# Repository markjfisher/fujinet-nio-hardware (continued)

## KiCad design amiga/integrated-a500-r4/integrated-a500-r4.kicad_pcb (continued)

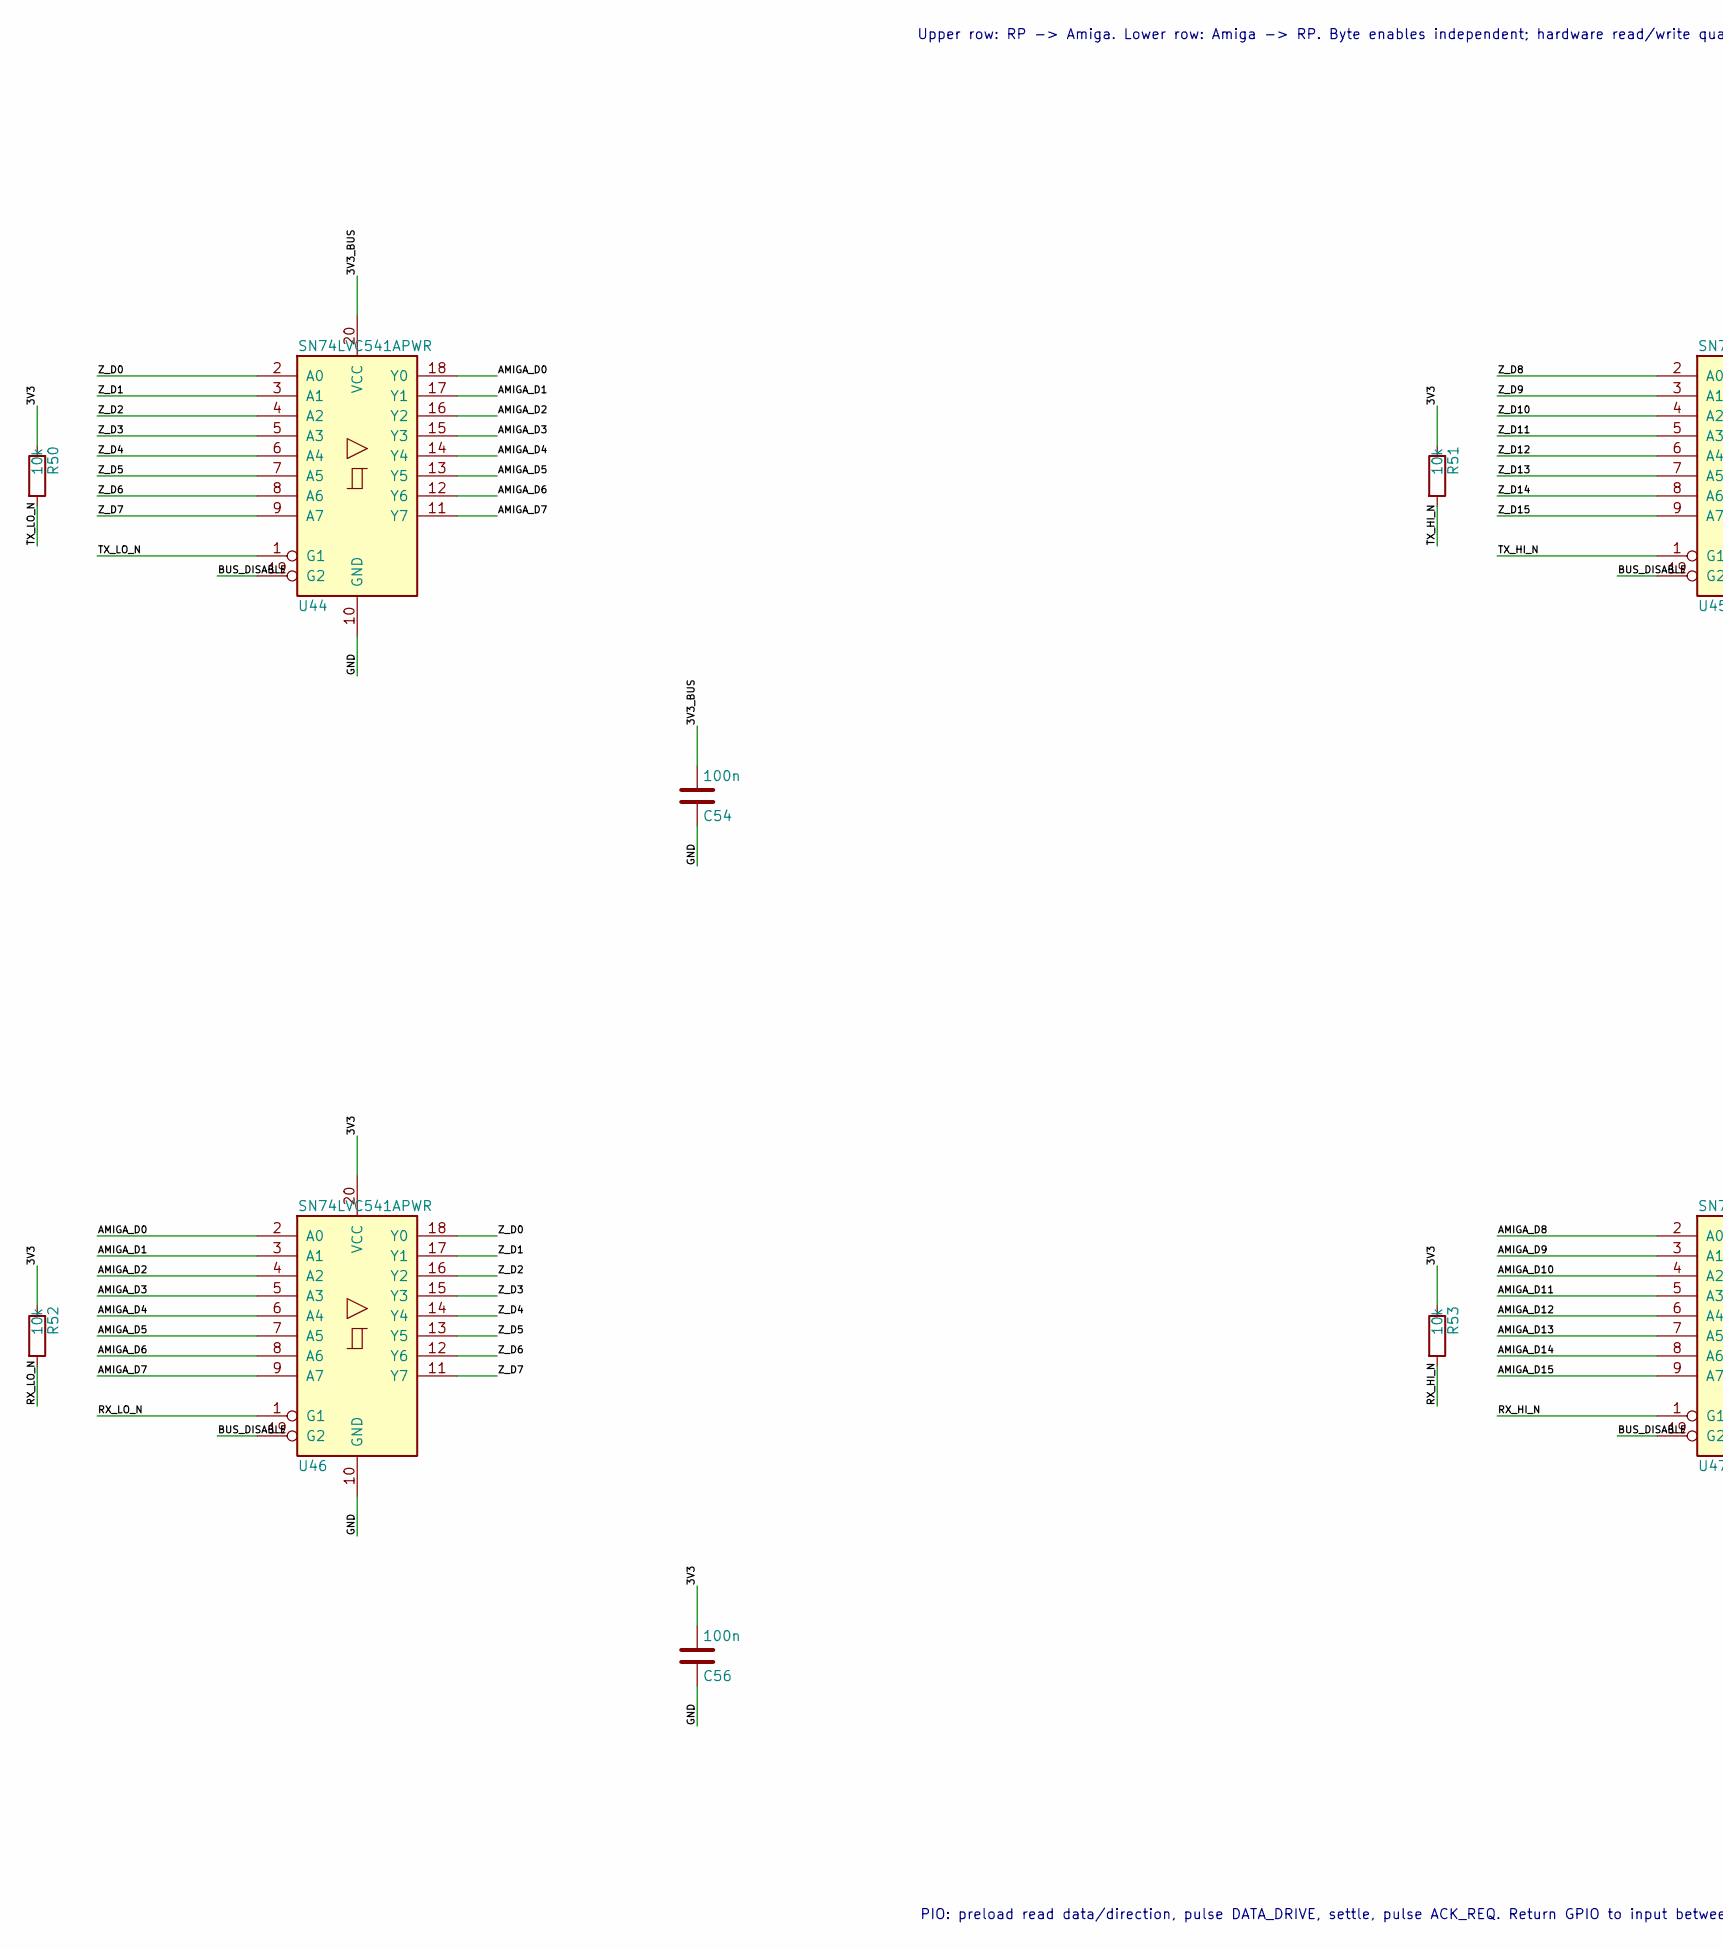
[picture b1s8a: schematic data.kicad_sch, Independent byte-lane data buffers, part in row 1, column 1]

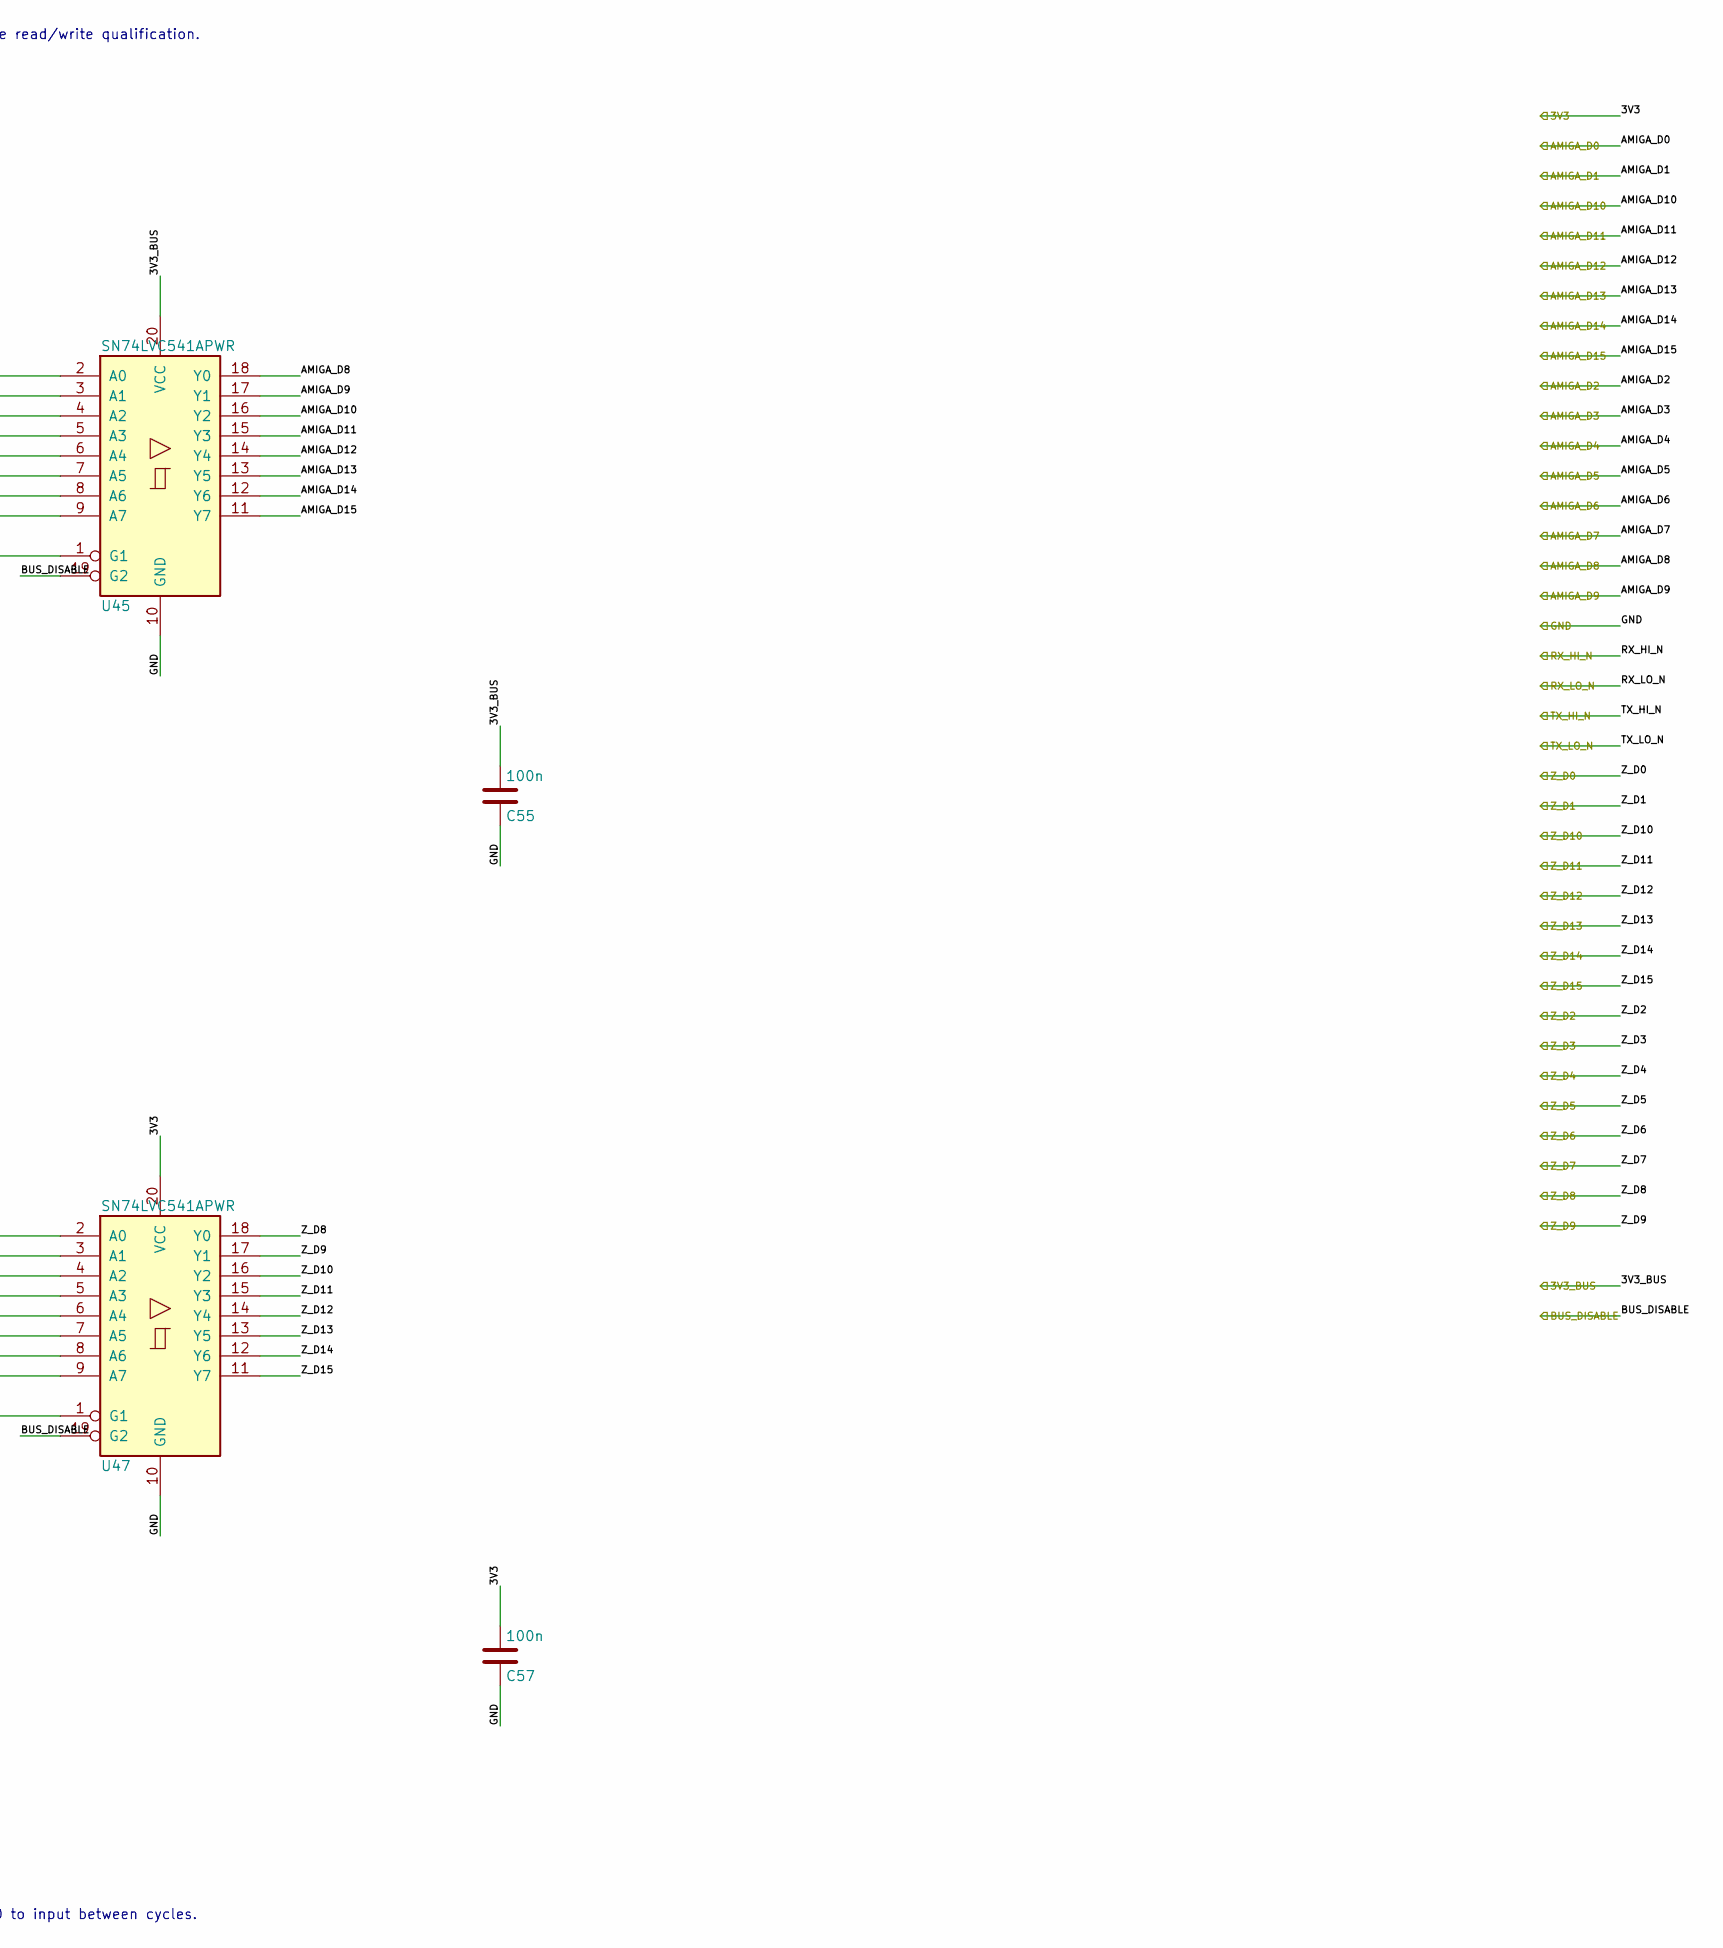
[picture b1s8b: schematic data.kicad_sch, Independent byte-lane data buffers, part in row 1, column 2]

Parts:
C54, C55, C56, C57: 100n; C_0603_1608Metric
R50, R51, R52, R53: 10k; R_0603_1608Metric
U44, U45, U46, U47: SN74LVC541APWR; TSSOP-20_4.4x6.5mm_P0.65mm

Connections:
/3V3: C56.1, C57.1, R50.1, R51.1, R52.1, R53.1, U46.20 (VCC), U47.20 (VCC); also elsewhere on the board
/3V3_BUS: C54.1, C55.1, U44.20 (VCC), U45.20 (VCC); also elsewhere on the board
/AMIGA_D0: U44.18 (Y0), U46.2 (A0); also elsewhere on the board
/AMIGA_D1: U44.17 (Y1), U46.3 (A1); also elsewhere on the board
/AMIGA_D2: U44.16 (Y2), U46.4 (A2); also elsewhere on the board
/AMIGA_D3: U44.15 (Y3), U46.5 (A3); also elsewhere on the board
/AMIGA_D4: U44.14 (Y4), U46.6 (A4); also elsewhere on the board
/AMIGA_D5: U44.13 (Y5), U46.7 (A5); also elsewhere on the board
/AMIGA_D6: U44.12 (Y6), U46.8 (A6); also elsewhere on the board
/AMIGA_D7: U44.11 (Y7), U46.9 (A7); also elsewhere on the board
/AMIGA_D8: U45.18 (Y0), U47.2 (A0); also elsewhere on the board
/AMIGA_D9: U45.17 (Y1), U47.3 (A1); also elsewhere on the board
/AMIGA_D10: U45.16 (Y2), U47.4 (A2); also elsewhere on the board
/AMIGA_D11: U45.15 (Y3), U47.5 (A3); also elsewhere on the board
/AMIGA_D12: U45.14 (Y4), U47.6 (A4); also elsewhere on the board
/AMIGA_D13: U45.13 (Y5), U47.7 (A5); also elsewhere on the board
/AMIGA_D14: U45.12 (Y6), U47.8 (A6); also elsewhere on the board
/AMIGA_D15: U45.11 (Y7), U47.9 (A7); also elsewhere on the board
/BUS_DISABLE: U44.19 (G2), U45.19 (G2), U46.19 (G2), U47.19 (G2); also elsewhere on the board
/RX_HI_N: R53.2, U47.1 (G1); also elsewhere on the board
/RX_LO_N: R52.2, U46.1 (G1); also elsewhere on the board
/TX_HI_N: R51.2, U45.1 (G1); also elsewhere on the board
/TX_LO_N: R50.2, U44.1 (G1); also elsewhere on the board
/Z_D0: U44.2 (A0), U46.18 (Y0); also elsewhere on the board
/Z_D1: U44.3 (A1), U46.17 (Y1); also elsewhere on the board
/Z_D2: U44.4 (A2), U46.16 (Y2); also elsewhere on the board
/Z_D3: U44.5 (A3), U46.15 (Y3); also elsewhere on the board
/Z_D4: U44.6 (A4), U46.14 (Y4); also elsewhere on the board
/Z_D5: U44.7 (A5), U46.13 (Y5); also elsewhere on the board
/Z_D6: U44.8 (A6), U46.12 (Y6); also elsewhere on the board
/Z_D7: U44.9 (A7), U46.11 (Y7); also elsewhere on the board
/Z_D8: U45.2 (A0), U47.18 (Y0); also elsewhere on the board
/Z_D9: U45.3 (A1), U47.17 (Y1); also elsewhere on the board
/Z_D10: U45.4 (A2), U47.16 (Y2); also elsewhere on the board
/Z_D11: U45.5 (A3), U47.15 (Y3); also elsewhere on the board
/Z_D12: U45.6 (A4), U47.14 (Y4); also elsewhere on the board
/Z_D13: U45.7 (A5), U47.13 (Y5); also elsewhere on the board
/Z_D14: U45.8 (A6), U47.12 (Y6); also elsewhere on the board
/Z_D15: U45.9 (A7), U47.11 (Y7); also elsewhere on the board

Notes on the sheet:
Upper row: RP -> Amiga. Lower row: Amiga -> RP. Byte enables independent; hardware read/write qualification.
PIO: preload read data/direction, pulse DATA_DRIVE, settle, pulse ACK_REQ. Return GPIO to input between cycles.

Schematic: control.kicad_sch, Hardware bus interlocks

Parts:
C70, C73, C75, C80, C81, C82, C86, C87, C88, C91, C93, C94, C95: 100n; C_0603_1608Metric
J60: BUS ARM (normally OPEN); PinHeader_1x02_P2.54mm_Vertical
R63, R64, R65, R66, R67: 10k; R_0603_1608Metric
U61, U66, U71: SN74LVC11APWR; TSSOP-14_4.4x5mm_P0.65mm
U64: SN74LVC04APWR; TSSOP-14_4.4x5mm_P0.65mm
U72, U73, U77, U78: SN74LVC1G10DBVR; SOT-23-6
U79: SN74LVC1G32DBVR; SOT-23-5
U82, U85: SN74LVC1G08DBVR; SOT-23-5
U84, U86: SN74LVC1G74DCUR; VSSOP-8_2.3x2mm_P0.5mm

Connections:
/3V3: C70.1, C73.1, C75.1, C80.1, C81.1, C82.1, C86.1, C87.1, C88.1, C91.1, C93.1, C94.1, C95.1, J60.1, U61.14 (VCC), U64.14 (VCC), U66.14 (VCC), U71.11 (3C), U71.14 (VCC), U72.5 (VCC), U72.6, U73.5 (VCC), U73.6, U77.5 (VCC), U77.6, U78.5 (VCC), U78.6, U79.5 (VCC), U82.5 (VCC), U84.7 (~PRE), U84.8 (VCC), U85.5 (VCC), U86.2 (D), U86.7 (~PRE), U86.8 (VCC); also elsewhere on the board
/ACK_REQ: R64.3; also elsewhere on the board
/ACK_REQ_C: U84.1 (C); also elsewhere on the board
/BUS_ARM: J60.2, R63.1; also elsewhere on the board
/BUS_ARM_C: U61.5 (2C); also elsewhere on the board
/BUS_PERMIT: U61.1 (1A), U61.2 (1B); also elsewhere on the board
/BUS_READY: R64.1; also elsewhere on the board
/BUS_READY_C: U61.11 (3C); also elsewhere on the board
/DATA_DRIVE_C: U86.1 (C); also elsewhere on the board
/HOST_BERR_N: U85.2; also elsewhere on the board
/HOST_RESET_N: U61.13 (1C); also elsewhere on the board
/Hardware bus interlocks/A20_LOW: U64.4 (2Y), U66.4 (2B)
/Hardware bus interlocks/ANY_LANE: U79.4, U84.2 (D)
/Hardware bus interlocks/AS_ACTIVE: U64.2 (1Y), U66.10 (3B)
/Hardware bus interlocks/CYCLE_OK: U66.8 (3Y), U71.1 (1A), U71.3 (2A), U71.9 (3A), U84.6 (~CLR), U86.6 (~CLR)
/Hardware bus interlocks/DATA_RECEIVE: U64.12 (6Y), U71.5 (2C)
/Hardware bus interlocks/DATA_VALID: U64.13 (6A), U71.13 (1C), U86.5 (Q)
/Hardware bus interlocks/HI_ACTIVE: U64.8 (4Y), U73.3, U78.3, U79.2
/Hardware bus interlocks/IO_TOP: U66.3 (2A), U66.12 (1Y)
/Hardware bus interlocks/IO_WINDOW: U66.6 (2Y), U66.11 (3C)
/Hardware bus interlocks/LO_ACTIVE: U64.6 (3Y), U72.3, U77.3, U79.1
/Hardware bus interlocks/READ_DRIVE: U71.12 (1Y), U72.1, U73.1
/Hardware bus interlocks/SAFE: U66.9 (3A), U82.1, U85.4
/Hardware bus interlocks/SAFE_BASE: U61.8 (3Y), U85.1
/Hardware bus interlocks/SAFE_MODE: U61.6 (2Y), U61.10 (3B)
/Hardware bus interlocks/SAFE_POWER: U61.9 (3A), U61.12 (1Y)
/Hardware bus interlocks/WAIT_PENDING: U71.10 (3B), U84.3 (~Q)
/Hardware bus interlocks/WRITE_CYCLE: U64.10 (5Y), U71.4 (2B)
/Hardware bus interlocks/WRITE_RECEIVE: U71.6 (2Y), U77.1, U78.1
/IRQ_REQ: R64.4; also elsewhere on the board
/IRQ_REQ_C: U82.2; also elsewhere on the board
/IRQ_SINK: U82.4; also elsewhere on the board
/RP_RUN_C: U61.3 (2A); also elsewhere on the board
/RUN_MODE_C: U61.4 (2B); also elsewhere on the board
/RX_HI_N: U78.4; also elsewhere on the board
/RX_LO_N: U77.4; also elsewhere on the board
/TX_HI_N: U73.4; also elsewhere on the board
/TX_LO_N: U72.4; also elsewhere on the board
/WAIT_SINK: U71.8 (3Y); also elsewhere on the board
/Z_A19: U66.5 (2C); also elsewhere on the board
/Z_A20: U64.3 (2A); also elsewhere on the board
/Z_A21: U66.13 (1C); also elsewhere on the board
/Z_A22: U66.2 (1B); also elsewhere on the board
/Z_A23: U66.1 (1A); also elsewhere on the board
/Z_AS_N: U64.1 (1A); also elsewhere on the board
/Z_LDS_N: U64.5 (3A); also elsewhere on the board
/Z_READ: U64.11 (5A), U71.2 (1B); also elsewhere on the board
/Z_UDS_N: U64.9 (4A); also elsewhere on the board

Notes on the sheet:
Host monitor: 0.405V x 11 = 4.455V nominal trip; CT open = 20ms release delay. No host supply drawn for operation.
XRDY wait starts in hardware for E80000-EFFFFF; rising ACK_REQ releases this cycle. No local DTACK driver.
U84/U86 clear between cycles: stale ACK/DATA_DRIVE cannot carry into next cycle. BERR disables all outputs.

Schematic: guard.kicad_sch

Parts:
C60, C111, C112, C118, C119: 1u 10V X7R; C_0603_1608Metric
C110, C120, C121, C122, C125, C126, C127, C128: 100n 10V X7R; C_0603_1608Metric
C113: 100u 6.3V polymer 20% ESR<=50m; CP_Elec_6.3x5.8
C114, C115, C116: 100p 25V C0G 5%; C_0603_1608Metric
C117: 220u 6.3V polymer 20% ESR<=50m; CP_Elec_6.3x5.8
D4: SS14-13-F; D_SMA
Q5: MMBT3904-7-F; SOT-23
R60: 102k 0.1%; R_0603_1608Metric
R61, R113, R115: 10k 0.1%; R_0603_1608Metric
R110: 133k 1%; R_0603_1608Metric
R111: 4.7k 1%; R_0603_1608Metric
R112, R114: 67.5k 0.1%; R_0603_1608Metric
R116, R122: 10k 1%; R_0603_1608Metric
R117, R118, R119, R121: 100k 1%; R_0603_1608Metric
R120: 22k 1%; R_0603_1608Metric
U60, U90, U91: MIC2790H-04VD6-TR; TSOT-23-6
U92: SN74LVC2G14DBVR; SOT-23-6
U93: SN74LVC2G132DCUR; VSSOP-8_2.3x2mm_P0.5mm
U94: SN74LVC2G125DCUR; VSSOP-8_2.3x2mm_P0.5mm
U95: TPS2553DBVR; SOT-23-6
U96: AP2112K-3.3TRG1; SOT-23-5
U97, U98, U100: 74LVC3G17DC,125; VSSOP-8_2.3x2mm_P0.5mm
U99: SN74LVC1G17DBVR; SOT-23-5

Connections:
/3V3: C117.1, C125.1, C126.1, C127.1, C128.1, R112.1, U97.8 (VCC), U98.8 (VCC), U99.5 (VCC), U100.8 (VCC); also elsewhere on the board
/3V3_BUS: C60.1, C112.1, C113.1, C118.1, C119.1, C120.1, C121.1, C122.1, R111.1, R114.1, R116.1, R117.1, R118.1, R119.1, U60.3 (~MR), U60.6 (VDD), U90.3 (~MR), U90.6 (VDD), U91.3 (~MR), U91.6 (VDD), U92.5 (VCC), U93.8 (VCC), U94.8 (VCC), U96.5 (VOUT); also elsewhere on the board
/ACK_REQ: U98.6 (3A); also elsewhere on the board
/ACK_REQ_C: U98.2 (3Y); also elsewhere on the board
/AMIGA_5V: C110.1, R60.1, U95.1 (IN), U95.3 (EN); also elsewhere on the board
/AMIGA_BERR_N: U100.3 (2A); also elsewhere on the board
/AMIGA_BERR_N_C: U100.5 (2Y); also elsewhere on the board
/AMIGA_DTACK_N: U100.6 (3A); also elsewhere on the board
/AMIGA_DTACK_N_C: U100.2 (3Y); also elsewhere on the board
/AMIGA_INT2_N: U94.3 (2Y); also elsewhere on the board
/AMIGA_RESET_N: U100.1 (1A); also elsewhere on the board
/AMIGA_RESET_N_C: U100.7 (1Y); also elsewhere on the board
/AMIGA_XRDY: U94.6 (1Y); also elsewhere on the board
/BUS_ARM: U97.6 (3A); also elsewhere on the board
/BUS_ARM_C: U97.2 (3Y); also elsewhere on the board
/BUS_DISABLE: R117.2, R120.1, U92.3 (2A), U92.6 (1Y); also elsewhere on the board
/BUS_PERMIT: R122.1, U92.4 (2Y), U93.1 (1A), U93.5 (2A); also elsewhere on the board
/BUS_READY: U98.1 (1A); also elsewhere on the board
/BUS_READY_C: U98.7 (1Y); also elsewhere on the board
/DATA_DRIVE_C: U98.5 (2Y); also elsewhere on the board
/Host interface power guard/BUS_CT: C116.1, U91.4 (CTH)
/Host interface power guard/BUS_SENSE: R114.2, R115.1, U91.5 (SNS)
/Host interface power guard/GUARD_OK_RAW: R116.2, U60.1 (~RESET), U90.1 (~RESET), U91.1 (~RESET), U92.1 (1A)
/Host interface power guard/GUARD_RESET_BASE: Q5.1 (B), R120.2, R121.1
/Host interface power guard/HOST_5V_LIMITED: D4.2 (A), U95.6 (OUT)
/Host interface power guard/HOST_CT: C114.1, U60.4 (CTH)
/Host interface power guard/HOST_ILIM: R110.1, U95.5 (ILIM)
/Host interface power guard/HOST_LDO_IN: C111.1, D4.1 (K), U96.1 (VIN), U96.3 (EN)
/Host interface power guard/HOST_SENSE: R60.2, R61.1, U60.5 (SNS)
/Host interface power guard/IRQ_OE_N: R119.2, U93.3 (2Y), U94.7 (~2OE)
/Host interface power guard/MAIN_CT: C115.1, U90.4 (CTH)
/Host interface power guard/MAIN_SENSE: R112.2, R113.1, U90.5 (SNS)
/Host interface power guard/WAIT_OE_N: R118.2, U93.7 (1Y), U94.1 (~1OE)
/IRQ_REQ: U99.2; also elsewhere on the board
/IRQ_REQ_C: U99.4; also elsewhere on the board
/IRQ_SINK: U93.6 (2B); also elsewhere on the board
/RP_RUN: Q5.3 (C), U97.1 (1A); also elsewhere on the board
/RP_RUN_C: U97.7 (1Y); also elsewhere on the board
/RUN_MODE: U97.3 (2A); also elsewhere on the board
/RUN_MODE_C: U97.5 (2Y); also elsewhere on the board
/WAIT_SINK: U93.2 (1B); also elsewhere on the board

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
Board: 4 copper layers, 203 parts (2 on the bottom side), 218 nets, no tracks yet.

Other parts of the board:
H1, H2, H3, H4: MountingHole_3.2mm_M3
